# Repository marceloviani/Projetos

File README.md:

## Projetos feitos por Marcelo Viani, Engenheiro Eletrônico formado pelo IFSC.

Estes projetos foram desenvolvidos durante matérias do curso ou projetos próprios.

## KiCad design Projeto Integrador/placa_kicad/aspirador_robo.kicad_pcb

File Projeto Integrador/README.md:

## Robô Aspirador de Pó

- Instituto Federal da Santa Catarina - Campus Florianópolis
- Nomes: Marcelo Viani e Matheus Rodrigues da Cunha
- Curso: Engenharia Eletrônica
- Unidade Curricular: Projeto Integrador 3

### INTRODUÇÃO

Um dos aparelhos eletrônicos que tem sido destaque nos últimos anos é o robô aspirador, esse equipamento limpa os locais de uma residência sem a necessidade de estar sendo manuseado por uma pessoa durante o seu funcionamento. Este dispositivo tem em comum em todos os modelos se movimentar em um ambiente de forma autônoma.

A grande maioria desse tipo de robô possui um sistema que anda de forma aleatória, podendo ou não realizar uma boa limpeza com uma baixa autonomia. Já os mais avançados, começam a ter funções como poder programar o horário de funcionamento, avisar quando a bateria estiver acabando, voltar de forma autônoma para a base de carregamento e realizar o mapeamento completo do ambiente.

Nossa proposta é montar um protótipo de robô aspirador, que possua todas as funções básicas vistas nesse tipo de dispositivo, como a limpeza autônoma, avisar quando a bateria estiver em nível baixo, evitar quedas e possíveis batidas. Há o objetivo de tentar realizar algumas atividades mais avançadas, sendo a principal, o desenvolvimento de um software que consiga realizar um mapeamento do ambiente ou que o robô trace uma rota de forma a passar em toda a área do local onde ele for colocado.

Necessidades:

- 1 Base/Case
- 2 Aspirar
- 3 Bateria
- 5 Evitar batidas
- 6 Evitar quedas
- 7 Registrar Movimentação
- 8 Controle

1 Base
- Como base para nosso projeto, utilizamos o [carrinho feito por Lucas Odair](https://github.com/luscasos/PI3-carro), para a locomoção do robô.
Para a parte de aspiração foi reaproveitado a base de armazenamento de poeira de um aspirador de pó convencional.

2 Aspirar
- Para girar a ventoinha de sucção foi utilizado um motor de 3V.

3 Bateria
- Para a movimentação do robô foram utilizadas em série duas baterias LIPO de 3,7V e 1200mAh.
- Para a aspiração foi utilizada separadamente uma bateria Li-ion de 3,7V e 4200mAh.

5 Evitar batidas
- Para evitar batidas foi utilizado o Sensor Ultrassônico HC-SR04, que permite a leitura de distâncias de 2 centímetros até 4 metros.

6 Evitar quedas
- Para evitar quedas, foram utilizados 2 Sensores ópticos TCRT5000, que possui um emissor infravermelho e um fototransistor como receptor.

7 Registrar Movimentação
- Para o registro da movimentação foram utilizados 2 sensores de velocidade encoder, que verificam a quantidade vezes que a transmissão de um sensor infravermelho é interrompida, para se saber o quanto foi andado.

8 Controle
- Para realizar o controle foi utilizado o controlador ATmega328p, devido a disponibilidade e conhecimento de uso.

Peças                                                                   | Valor       | Link
:---------------------------------------------------------------------: | :------:    | :----------------------:
Kit Chassi Robô (Utilizado do IFSC)                                     | R$ 132,90   | https://www.eletrogate.com/kit-chassi-4wd-robo-para-arduino
Motor DC 3V                                                             | R$ 6,90     | https://www.filipeflop.com/produto/mini-motor-dc-3v/
ATmega328p - Arduino UNO (Já possuía)                                   | R$ 106,95   | https://www.baudaeletronica.com.br/arduino-uno-r3-compativel-cabo-usb-atmega328-smd.html
BATERIA 3,7V 4200MAH (Já possuía)                                       | R$ 115,00   | https://www.casadapilha.com.br/bateria-icr26650-lith-recarregavel
Sensor HC-SR04 (Utilizado do IFSC)                                      | R$ 12,50    | https://www.robocore.net/sensor-robo/sensor-de-distancia-ultrassonico-hc-sr04
Sensor óptico TCRT5000 (Utilizado do IFSC)                              | R$ 3,70     | https://www.eletrogate.com/sensor-optico-reflexivo-tcrt5000
Sensor de Velocidade Encoder (Utilizado do IFSC)                        | R$ 7,50    | https://www.eletrogate.com/sensor-de-velocidade-encoder

## Desenvolvimento:

Foi desenvolvido todo suporte para que pudéssemos acoplar o módulo de aspiração no carrinho, para isso, foi utilizada a impressora 3D, que também foi utilizada para conseguirmos acoplar o motor comprado na peça de aspiração do aspirador. 
A produção da placa de circuito impresso foi realizada no IFSC utilizando software Kicad, com o circuito sendo apresentado na figura abaixo, tendo o motor e um capacitor em paralelo com o diodo 1N4181, que ficaram acoplados diretamente na base do aspirador:

 Placa de desenvolvida: 

O protótipo do robô está apresentado na figura abaixo:

O código foi desenvolvido utilizando o software eclipse, configurado para a programação de microcontroladores AVR.

## Conclusão:

Durante o desenvolvimento do projeto, foi visto que o mapeamento de um lugar pode ser feito de diversas formas, sendo possível aplicar novas tecnologias que possibilitam até um completo mapeamento tridimensional, porém, para isso é necessário o uso de controladores de maior capacidade e o uso de softwares que ajudem na criação desses mapas.

Contudo, é possível a aplicação de controladores mais simples, realizando um mapeamento mais simples ou simplesmente conduzindo o robô para fazer uma rota de forma mais eficiente, algo que pode ser mais vantajoso que a pesada aplicação de software.

Apesar das dificuldades, conseguimos montar o robô aspirador, que apesar de se forem somados os valores de seus componentes, esse valor ultrapassar os 300 reais, nosso maior gasto foi a compra de um motor de 3V, pois todo o resto foi reaproveitado do que tínhamos, do que poderíamos utilizar do IFSC e de materiais que conseguimos reaproveitar.

## Referência e Bibliografia:

- https://cdn.sparkfun.com/datasheets/Sensors/Proximity/HCSR04.pdf
- https://www.tecmundo.com.br/produto/207430-aspiradores-robo-tiveram-aumento-vendas-372-em-2020.htm
- https://www.teses.usp.br/teses/disponiveis/3/3139/tde-17012022-100444/fr.php

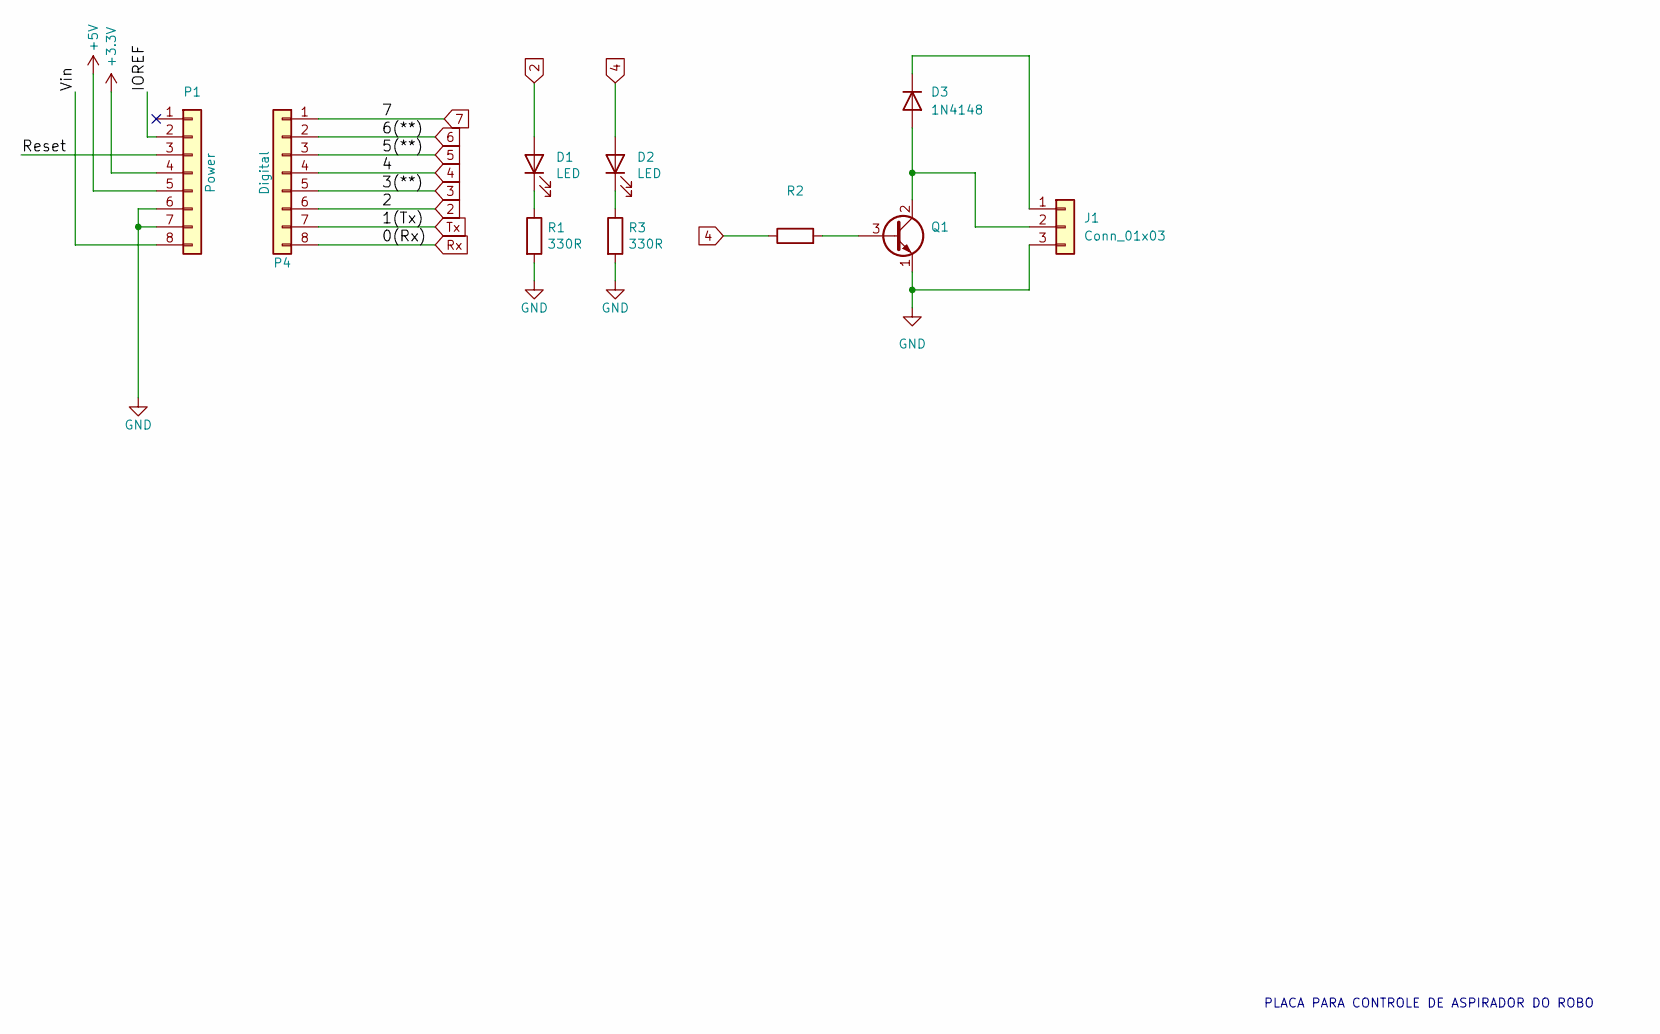
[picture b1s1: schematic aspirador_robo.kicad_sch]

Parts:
D1, D2: LED; LED_D5.0mm
D3: 1N4148; D_DO-35_SOD27_P7.62mm_Horizontal
J1: Conn_01x03; PinSocket_1x03_P2.54mm_Vertical
P1: Power
P4: Digital
Q1: (no value)
R1, R3: 330R; R_Axial_DIN0207_L6.3mm_D2.5mm_P10.16mm_Horizontal
R2: (no value)

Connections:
2: D1.2 (A), P4.6
3: P4.5
4: D2.2 (A), P4.4, R2.1
5: P4.3
6: P4.2
7: P4.1
+3V3: P1.4
+5V: P1.5
/IOREF: P1.2
/Reset: P1.3
/Vin: P1.8
GND: J1.3, P1.6, P1.7, Q1.1 (E), R1.2, R3.2
unnamed: D1.1 (K), R1.1
unnamed: D2.1 (K), R3.1
unnamed: D3.1 (K), J1.1
unnamed: D3.2 (A), J1.2, Q1.2 (C)
unnamed: Q1.3 (B), R2.2
Rx: P4.8
Tx: P4.7

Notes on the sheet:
PLACA PARA CONTROLE DE ASPIRADOR DO ROBO

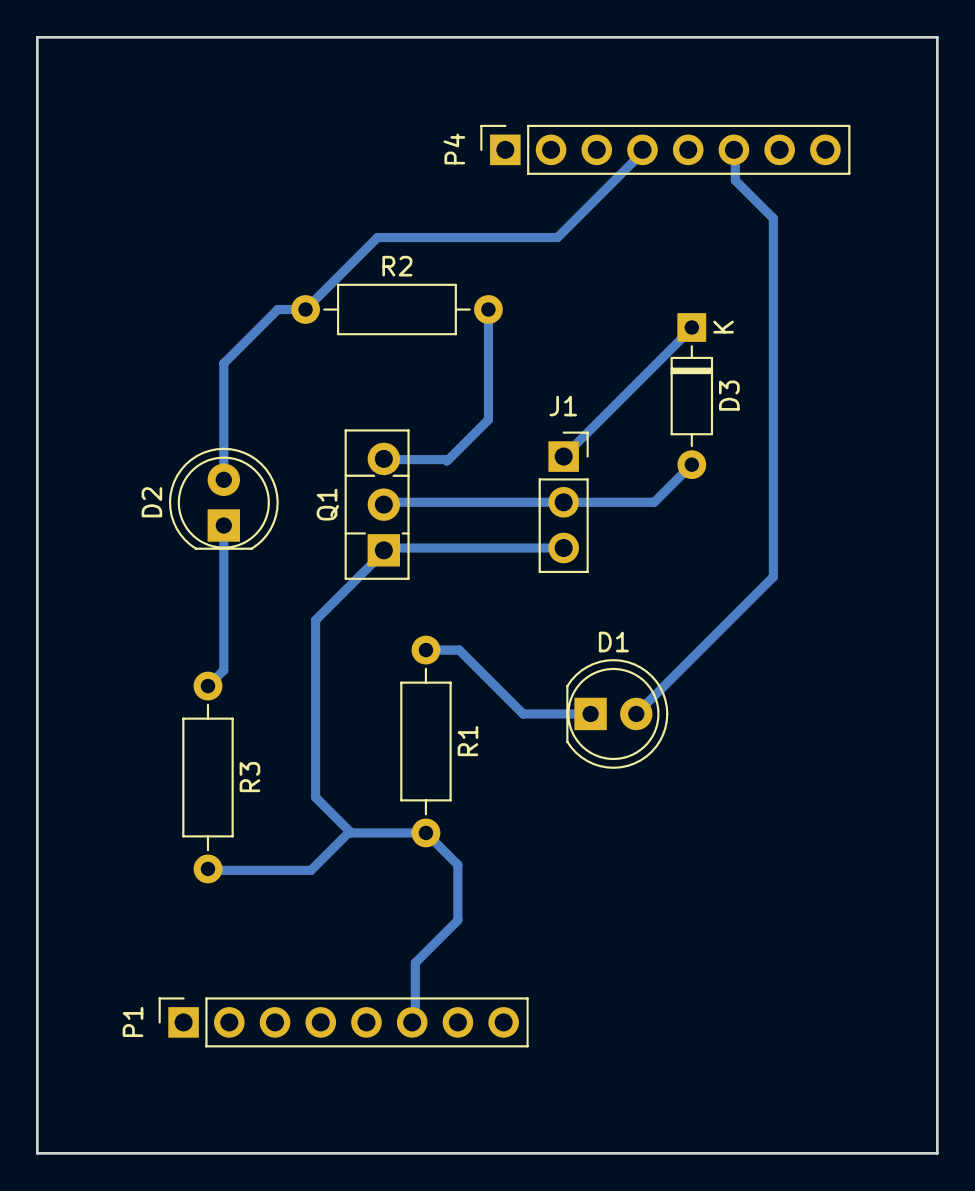
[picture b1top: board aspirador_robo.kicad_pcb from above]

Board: 2 copper layers, 50.0 x 62.0 mm, 10 parts (0 on the bottom side), 8 nets.

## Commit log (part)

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2020-02-18 Microcontroladores - AVR
2020-02-18 Projetos
2020-02-18 adicionando projeto integrador 2
2020-02-18 projeto de eletronica digital
2022-06-01 Create TCC___Victor_Tadashi.pdf?sequence=1&isAllowed=y
